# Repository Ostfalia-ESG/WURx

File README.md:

# Wake-up Receiver (WURx)
This project includes the main PCB design as well as the software for a semi-active Wake-up Receiver with addressing capabilities.

The WURx is the green part of the overall architecture shown in the following figure.
More details are found in the associated publications ([HotWire], [STFO]).

## Features
This implementation is an experimental solution for research purposes and has the following functions:

- Different comparators in the frontend are possible (TLV3691, LPV7215, TS881)
- Configurable address
- Configurable address length (0 to 32 bit)
- Configurable bitrate (100 to 25.6 kbps, with automatic clock adjustment)
- Backend supports deep-sleep and Switch (by) Transistors Fully Off (STFO) mode (see [STFO])

## Requirements
- Hardware
  - The PCBs (frontend and backend) designed in KiCad (see folder pcb/)
  - A transmitter (e.g. a Software Defined Radio like the USRP B210 with GNU Radio) is needed to send a Wake-up Call
- To program the $\mu C$ (a PIC16LF1823)
    - [MPLAB&reg; X IDE](https://www.microchip.com/en-us/tools-resources/develop/mplab-x-ide#)
    - [MPLAB&reg; XC8 C-Compiler](https://www.microchip.com/en-us/tools-resources/develop/mplab-xc-compilers/downloads-documentation#XC8)

## UART interface

[HotWire]: https://paper1
[STFO]: https://paper2

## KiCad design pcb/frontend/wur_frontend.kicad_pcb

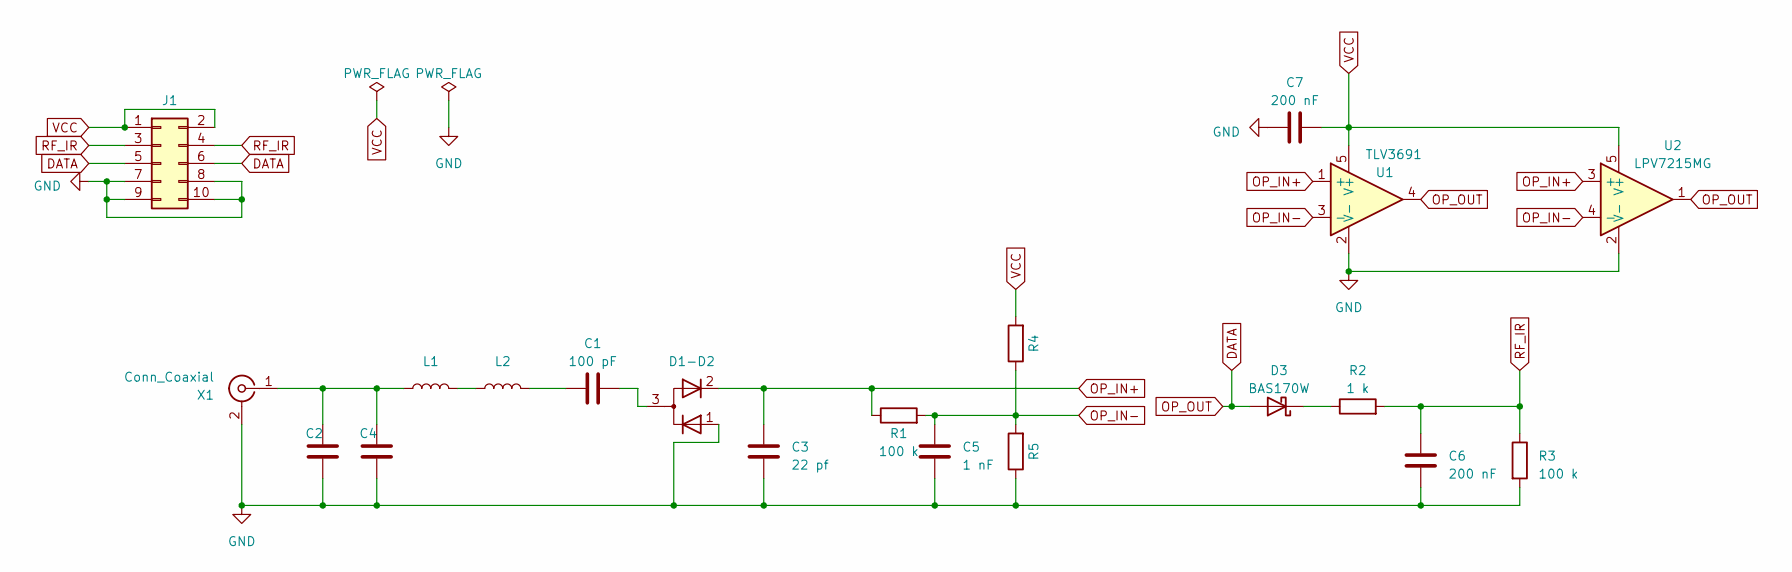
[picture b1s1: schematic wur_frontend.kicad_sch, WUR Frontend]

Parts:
C1: 100 pF; C_0603_1608Metric_Pad1.08x0.95mm_HandSolder
C2, C4: C_0603_1608Metric_Pad1.08x0.95mm_HandSolder
C3: 22 pf; C_0603_1608Metric_Pad1.08x0.95mm_HandSolder
C5: 1 nF; C_0603_1608Metric_Pad1.08x0.95mm_HandSolder
C6, C7: 200 nF; C_0603_1608Metric_Pad1.08x0.95mm_HandSolder
D1-D2: SOT-23
D3: BAS170W; D_SOD-323_HandSoldering
J1: Conn_02x05_Odd_Even; PinHeader_2x05_P2.54mm_Vertical
L1, L2: L; L_0603_1608Metric_Pad1.05x0.95mm_HandSolder
R1, R3: 100 k; R_0603_1608Metric_Pad0.98x0.95mm_HandSolder
R2: 1 k; R_0603_1608Metric_Pad0.98x0.95mm_HandSolder
R4, R5: R_0603_1608Metric_Pad0.98x0.95mm_HandSolder
U1: TLV3691; DCK_SC70
U2: LPV7215MG; DCK_SC70
X1: Conn_Coaxial; SMA_Amphenol_132289_EdgeMount

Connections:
DATA: D3.2 (A), J1.5, J1.6, U1.4, U2.1
GND: C2.2, C3.1, C4.2, C5.1, C6.1, C7.1, D1-D2.1 (K), J1.7, J1.8, J1.9, J1.10, R3.2, R5.1, U1.2 (V-), U2.2 (V-), X1.2 (Ext)
unnamed: C1.1, L2.2
unnamed: C1.2, D1-D2.3 (A)
unnamed: D3.1 (K), R2.1
unnamed: L1.2, L2.1
unnamed: C2.1, C4.1, L1.1, X1.1 (In)
OP_IN+: C3.2, D1-D2.2 (K), R1.1, U1.1 (+), U2.3 (+)
OP_IN-: C5.2, R1.2, R4.1, R5.2, U1.3 (-), U2.4 (-)
RF_IR: C6.2, J1.3, J1.4, R2.2, R3.1
VCC: C7.2, J1.1, J1.2, R4.2, U1.5 (V+), U2.5 (V+)

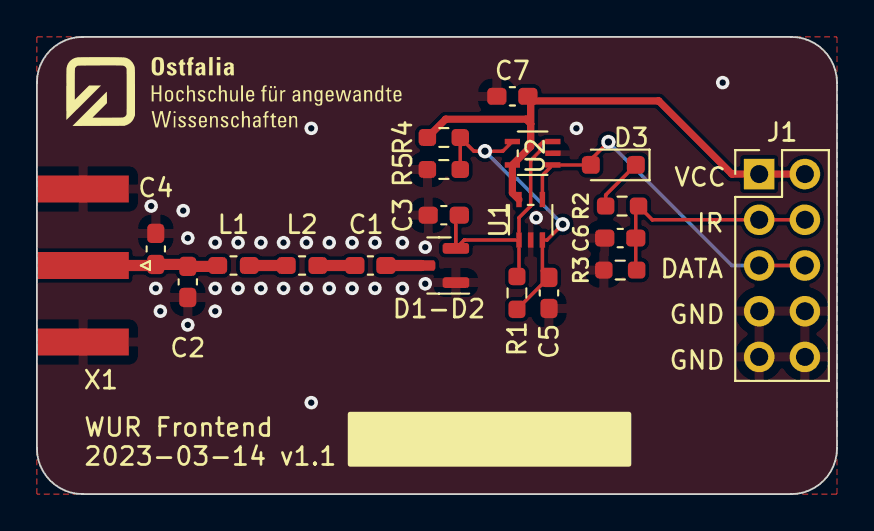
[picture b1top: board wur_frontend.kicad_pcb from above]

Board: 2 copper layers, 44.5 x 25.4 mm, 20 parts (0 on the bottom side), 11 nets.

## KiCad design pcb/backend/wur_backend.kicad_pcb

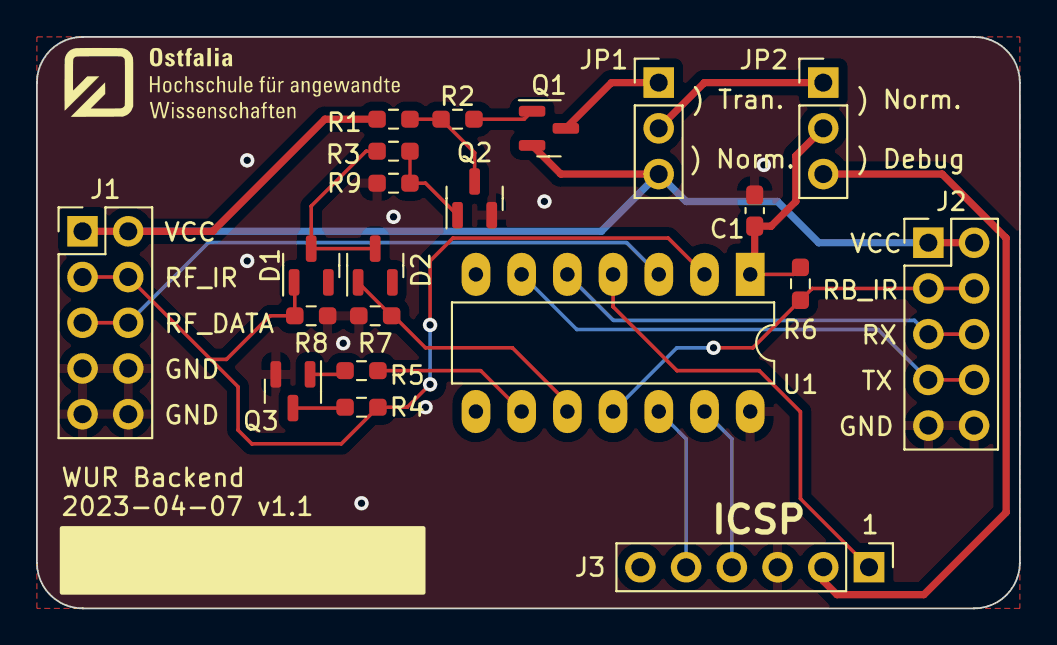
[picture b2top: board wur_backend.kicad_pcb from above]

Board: 2 copper layers, 54.6 x 31.8 mm, 21 parts (0 on the bottom side), 22 nets.

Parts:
C1: 100 nF; C_0603_1608Metric_Pad1.08x0.95mm_HandSolder
D1, D2: SMMBD701LT1G; SOT-23
J1, J2: Conn_02x05_Odd_Even; PinHeader_2x05_P2.54mm_Vertical
J3: Conn_01x06; PinHeader_1x06_P2.54mm_Vertical
JP1, JP2: Jumper_3_Open; PinHeader_1x03_P2.54mm_Vertical
Q1: BC857; SOT-23
Q2, Q3: BC847; SOT-23
R1: 100 meg; R_0603_1608Metric_Pad0.98x0.95mm_HandSolder
R2: 330 k; R_0603_1608Metric_Pad0.98x0.95mm_HandSolder
R3, R9: 1 meg; R_0603_1608Metric_Pad0.98x0.95mm_HandSolder
R4: 100 Ohm; R_0603_1608Metric_Pad0.98x0.95mm_HandSolder
R5: 2.2 kOhm; R_0603_1608Metric_Pad0.98x0.95mm_HandSolder
R6: 100k; R_0603_1608Metric_Pad0.98x0.95mm_HandSolder
R7, R8: 10 meg; R_0603_1608Metric_Pad0.98x0.95mm_HandSolder
U1: DIP-14_W7.62mm_LongPads

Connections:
/RF_DISCHARGE: R5.1, U1.9 (SDI/SDA/RC1)
GND: C1.2, J1.7, J1.8, J1.9, J1.10, J2.9, J2.10, J3.3, Q2.2 (E), Q3.2 (E), R7.2, R8.1, R9.1, U1.14 (VSS)
unnamed: C1.1, JP2.2 (C), R6.1, U1.1 (VDD)
unnamed: D1.3, D2.3, R3.2
unnamed: JP1.1 (A), Q1.3 (C)
unnamed: JP1.2 (C), JP2.1 (A)
unnamed: Q1.1 (B), R2.1
unnamed: Q2.1 (B), R3.1, R9.2
unnamed: Q2.3 (C), R1.2, R2.2
unnamed: Q3.1 (B), R5.2
unnamed: Q3.3 (C), R4.1
P_ICSPCLK: J3.5, U1.12 (RA1/D-/ICSPCLK)
P_ICSPDAT: J3.4, U1.13 (RA0/D+/ICSPDAT)
P_VCC: J3.2, JP2.3 (B)
P_VPP_\MCLR: J3.1, U1.4 (RA3/T1G/~SS/~MCLR/Vpp)
RB_IR/CONF_EN: J2.3, J2.4, R6.2, U1.11 (RA2/C1OUT/T0CKI)
RF_DATA: J1.5, J1.6, U1.3 (RA4/T1G/SDO/CLKOUT/OSC2/CLKR)
RF_IR: D1.1, J1.3, J1.4, R4.2, R8.2, U1.2 (RA5/T1CKI/CLKIN/OSC1)
RF_IR_HOLD: D2.1, R7.1, U1.10 (SCK/SCL/RC0)
RX: J2.5, J2.6, U1.5 (DT/RX/RC5)
TX: J2.7, J2.8, U1.6 (CK/TX/RC4)
VCC: J1.1, J1.2, J2.1, J2.2, JP1.3 (B), Q1.2 (E), R1.1

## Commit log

2023-07-29 add pcb design
2023-07-29 add software
2023-08-21 fix bug for empty address

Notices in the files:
parts and their libraries:
Copyright 2021 Accelerated Designs. All rights reserved.
